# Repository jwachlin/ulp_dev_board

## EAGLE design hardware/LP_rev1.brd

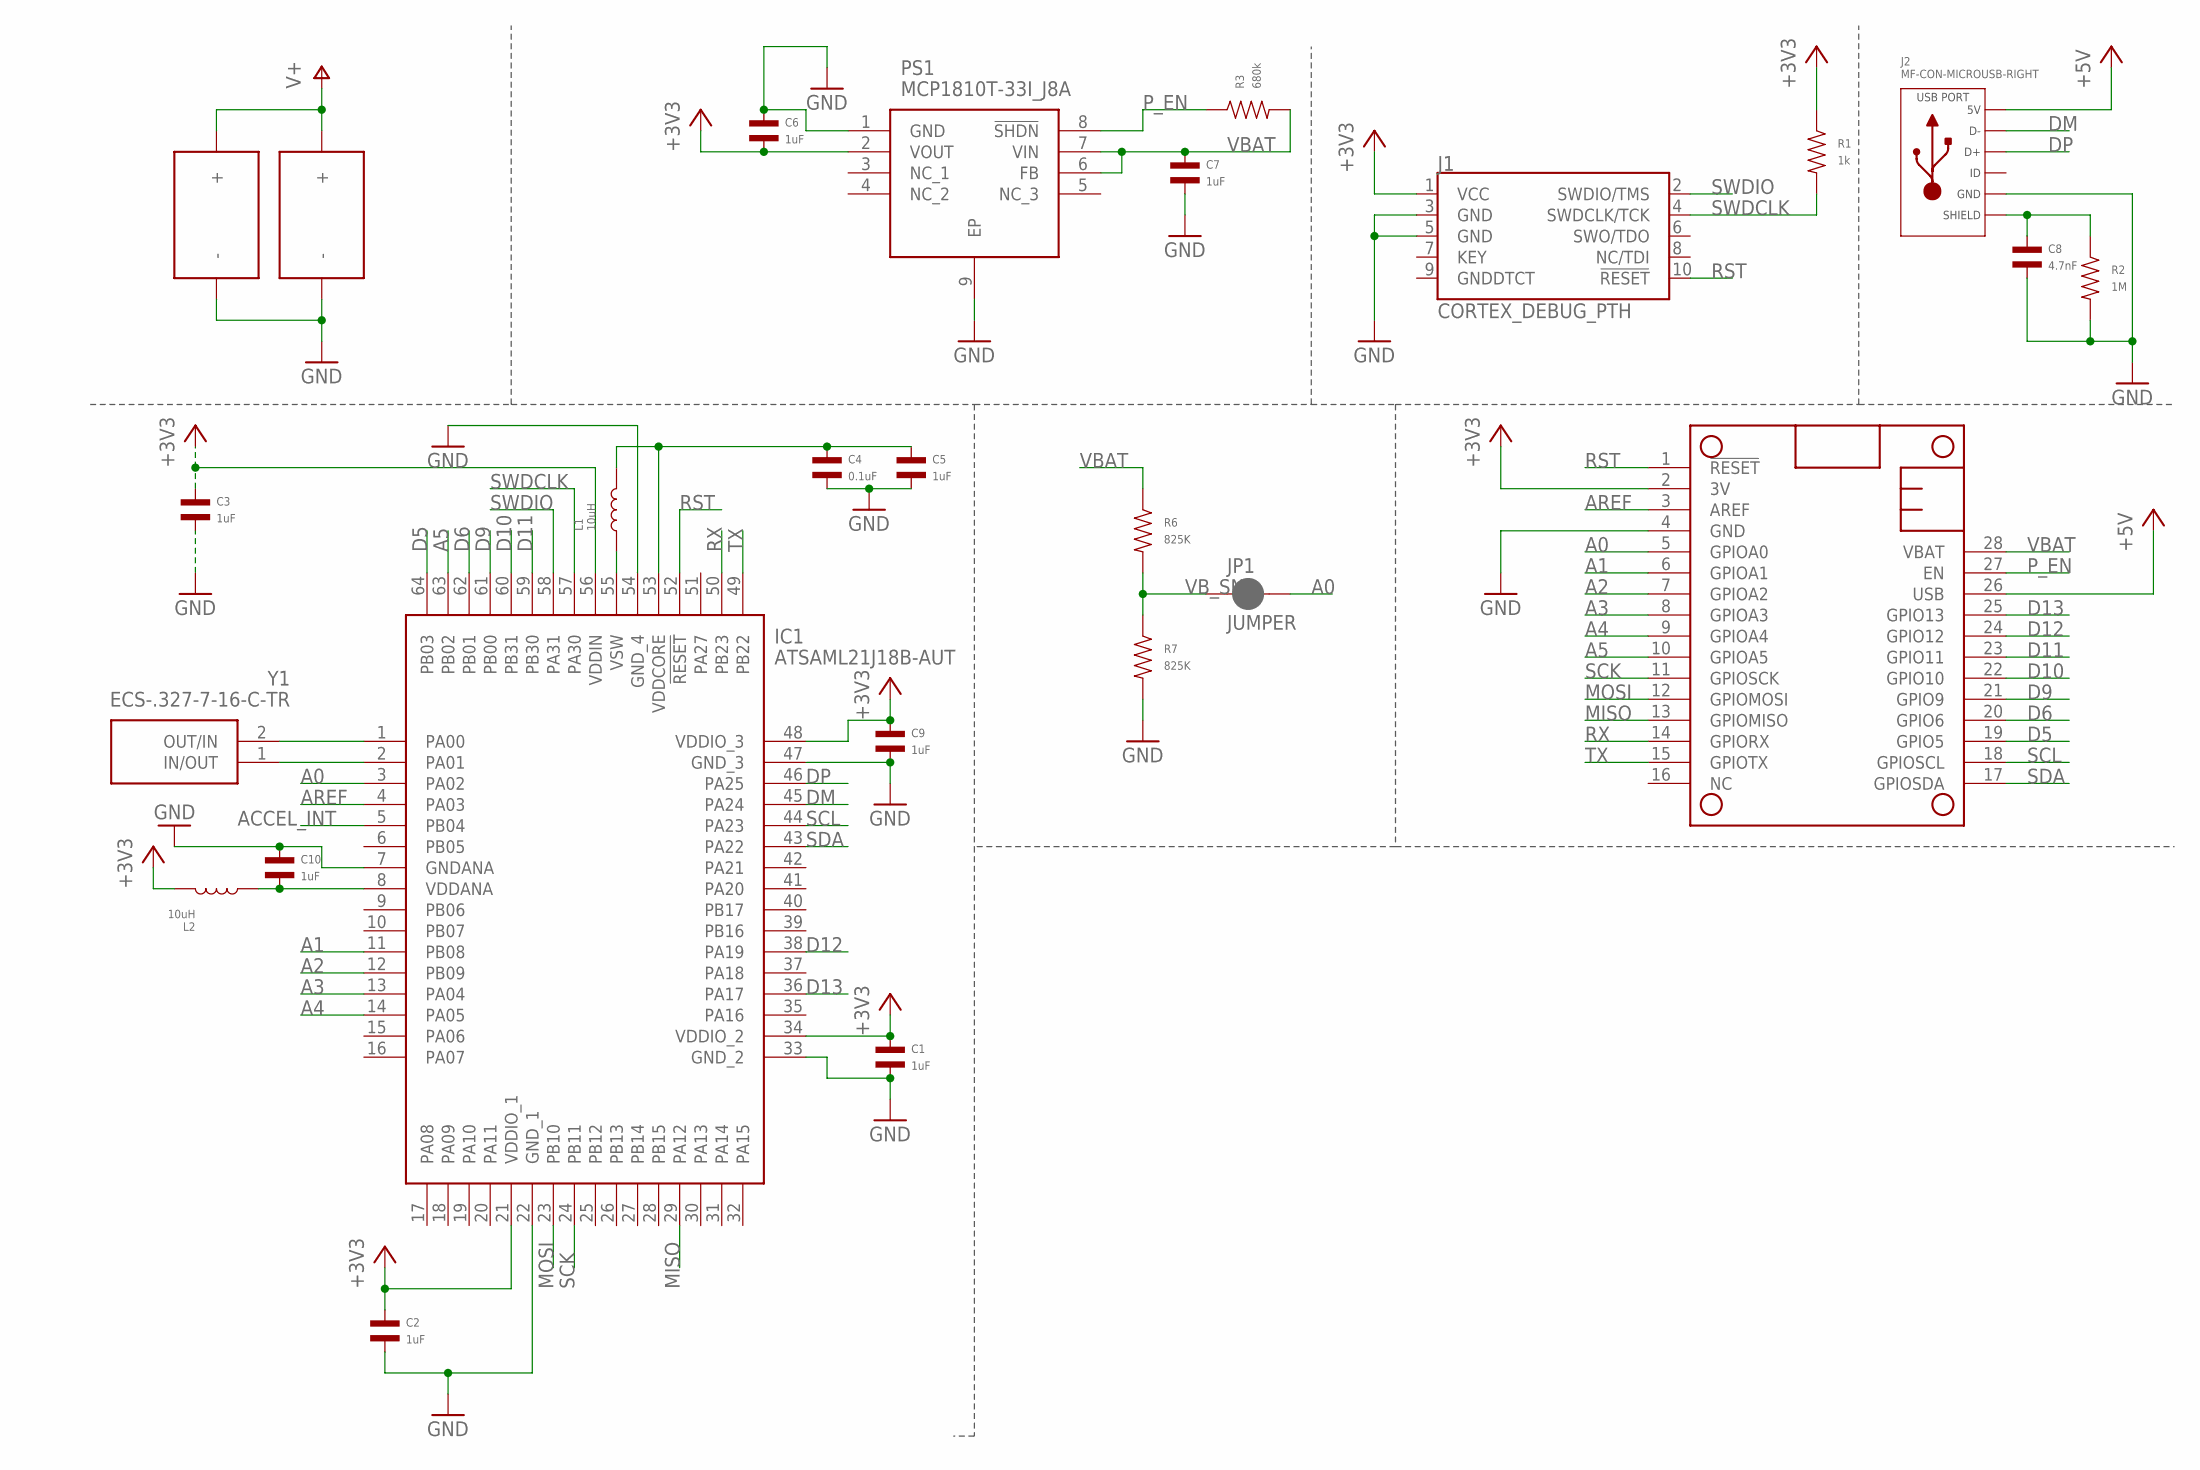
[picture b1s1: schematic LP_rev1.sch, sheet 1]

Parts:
C1, C2, C3, C5, C6, C7, C9, C10: 1uF; C0402
C4: 0.1uF; C0402
C8: 4.7nF; C0402
IC1: ATSAML21J18B-AUT; QFP50P1200X1200X120-64N
J1: CORTEX_DEBUG_PTH; 2X5-PTH-1.27MM
J2: MF-CON-MICROUSB-RIGHT; MICROUSB-RIGHT
JP1: JUMPER; SMT-JUMPER_2_NC_PASTE_NO-SILK
L1, L2: 10uH; L0603
MS1: FEATHERWING
PS1: MCP1810T-33I_J8A; SON50P200X200X90-9N
R1: 1k; R0402
R2: 1M; R0402
R3: 680k; R0402
R6, R7: 825K; R0402
U$1, U$2: KXOB25-01X8F
Y1: ECS-.327-7-16-C-TR; ECS327516TR

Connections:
+3V3: C1.P$1, C2.P$1, C3.P$1, C6.P$2, C9.P$1, IC1.21 (VDDIO_1), IC1.34 (VDDIO_2), IC1.48 (VDDIO_3), IC1.56 (VDDIN), J1.1 (VCC), L2.P$2, MS1.2 (3V), PS1.2 (VOUT), R1.P$1; also elsewhere on the board
+5V: J2.1 (5V), MS1.26 (USB)
A0: IC1.3 (PA02), JP1.2, MS1.5 (GPIOA0)
A1: IC1.11 (PB08), MS1.6 (GPIOA1)
A2: IC1.12 (PB09), MS1.7 (GPIOA2)
A3: IC1.13 (PA04), MS1.8 (GPIOA3)
A4: IC1.14 (PA05), MS1.9 (GPIOA4)
A5: IC1.63 (PB02), MS1.10 (GPIOA5)
ACCEL_INT: IC1.5 (PB04); also elsewhere on the board
AREF: IC1.4 (PA03), MS1.3 (AREF)
D5: IC1.64 (PB03), MS1.19 (GPIO5)
D6: IC1.62 (PB01), MS1.20 (GPIO6)
D9: IC1.61 (PB00), MS1.21 (GPIO9)
D10: IC1.60 (PB31), MS1.22 (GPIO10)
D11: IC1.59 (PB30), MS1.23 (GPIO11)
D12: IC1.38 (PA19), MS1.24 (GPIO12)
D13: IC1.36 (PA17), MS1.25 (GPIO13)
DM: IC1.45 (PA24), J2.2 (D-)
DP: IC1.46 (PA25), J2.3 (D+)
GND: C1.P$2, C2.P$2, C3.P$2, C4.P$2, C5.P$2, C6.P$1, C7.P$2, C8.P$2, C9.P$2, C10.P$1, IC1.7 (GNDANA), IC1.22 (GND_1), IC1.33 (GND_2), IC1.47 (GND_3), IC1.54 (GND_4), J1.3 (GND), J1.5 (GND), J2.5 (GND), MS1.4 (GND), PS1.1 (GND), PS1.9 (EP), R2.P$2, R7.P$2, U$1.P$2 (-), U$2.P$2 (-); also elsewhere on the board
MISO: IC1.29 (PA12), MS1.13 (GPIOMISO)
MOSI: IC1.23 (PB10), MS1.12 (GPIOMOSI)
unnamed: C4.P$1, C5.P$1, IC1.53 (VDDCORE), L1.P$2
unnamed: IC1.1 (PA00), Y1.2 (OUT/IN)
unnamed: IC1.2 (PA01), Y1.1 (IN/OUT)
unnamed: C10.P$2, IC1.8 (VDDANA), L2.P$1
unnamed: C8.P$1, J2.S1 (SLD), J2.S2 (SLD), J2.S3 (SLD), J2.S4 (SLD), J2.S5 (SLD), J2.S6 (SLD), R2.P$1
unnamed: IC1.55 (VSW), L1.P$1
P_EN: MS1.27 (EN), PS1.8 (!SHDN), R3.P$1
RST: IC1.52 (!RESET), J1.10 (!RESET), MS1.1 (!RESET)
RX: IC1.50 (PB23), MS1.14 (GPIORX)
SCK: IC1.24 (PB11), MS1.11 (GPIOSCK)
SCL: IC1.44 (PA23), MS1.18 (GPIOSCL); also elsewhere on the board
SDA: IC1.43 (PA22), MS1.17 (GPIOSDA); also elsewhere on the board
SWDCLK: IC1.57 (PA30), J1.4 (SWDCLK/TCK), R1.P$2
SWDIO: IC1.58 (PA31), J1.2 (SWDIO/TMS)
TX: IC1.49 (PB22), MS1.15 (GPIOTX)
V+: U$1.P$1 (+), U$2.P$1 (+); also elsewhere on the board
VBAT: C7.P$1, MS1.28 (VBAT), PS1.6 (FB), PS1.7 (VIN), R3.P$2, R6.P$1; also elsewhere on the board
VB_SNS: JP1.1, R6.P$2, R7.P$1

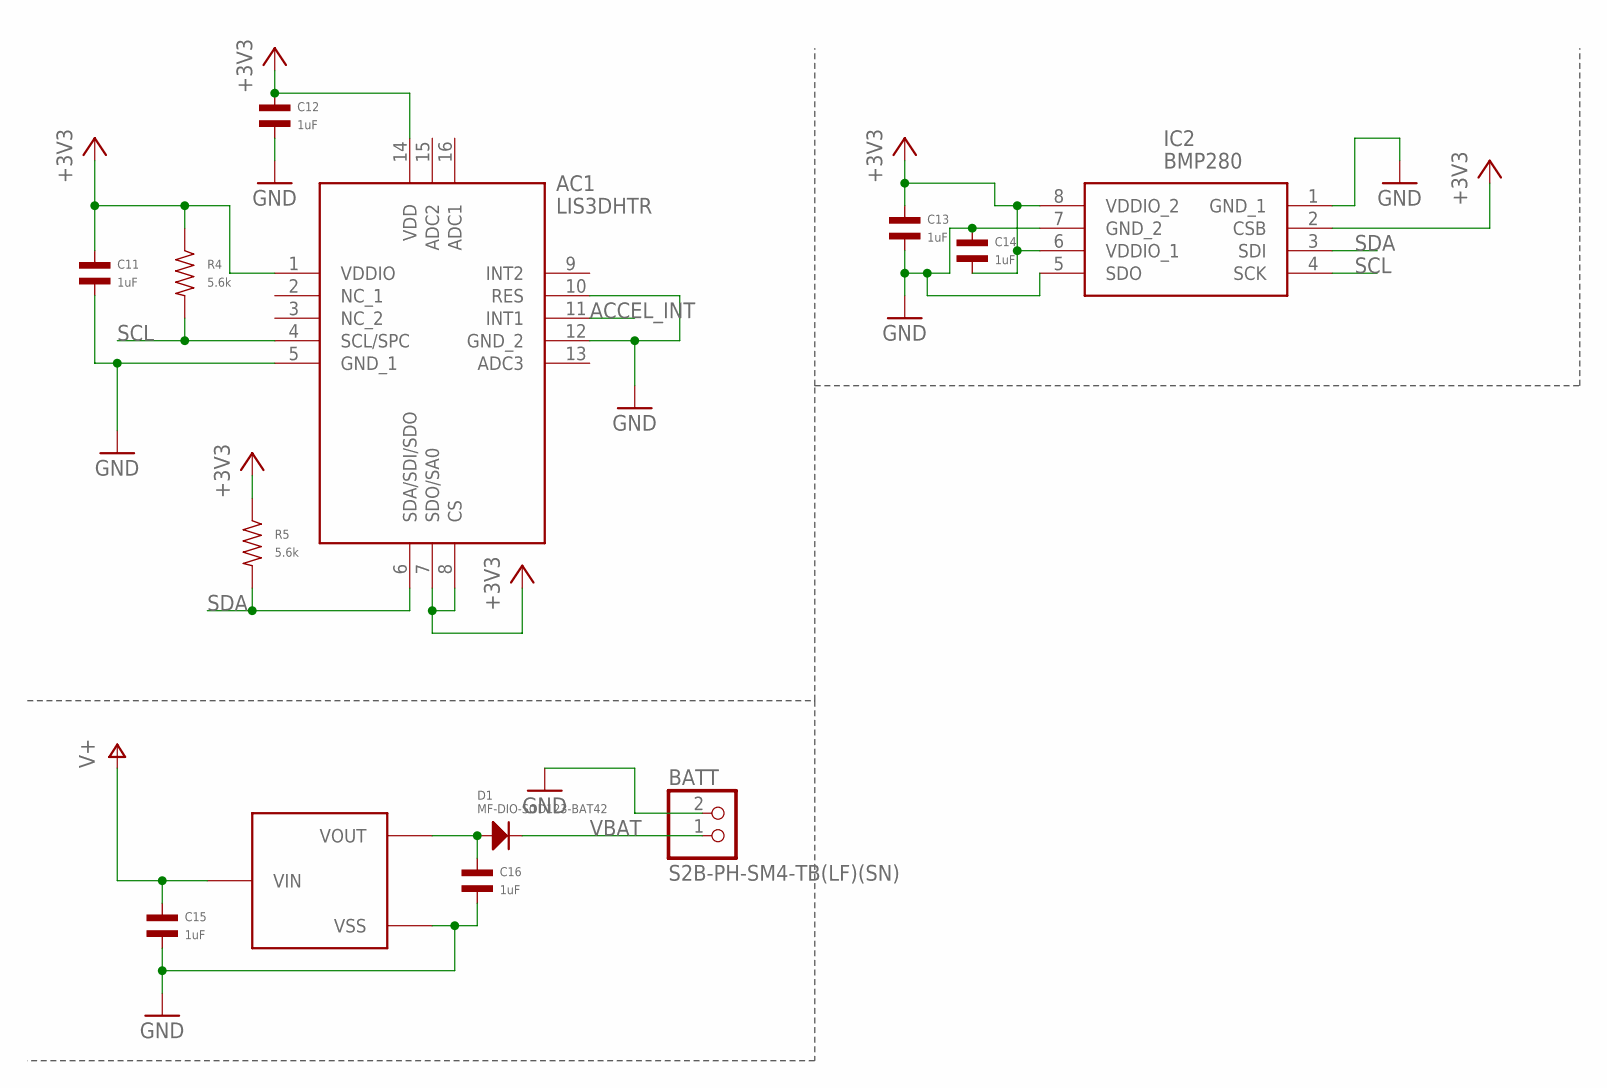
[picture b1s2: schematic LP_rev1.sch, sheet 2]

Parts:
AC1: LIS3DHTR; PQFN50P300X300X100-16N
BATT: S2B-PH-SM4-TB(LF)(SN); JST-PH-2-SMT-RA
C11, C12, C13, C14, C15, C16: 1uF; C0402
D1: MF-DIO-SOD123-BAT42; SOD-123
IC2: BMP280; 8-PIN-METAL-LID-LGA
R4, R5: 5.6k; R0402
U$3: XC6206P422MR-G; XC6206

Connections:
+3V3: AC1.1 (VDDIO), AC1.7 (SDO/SA0), AC1.8 (CS), AC1.14 (VDD), C11.P$1, C12.P$1, C13.P$1, C14.P$2, IC2.2 (CSB), IC2.6 (VDDIO_1), IC2.8 (VDDIO_2), R4.P$1, R5.P$1; also elsewhere on the board
ACCEL_INT: AC1.11 (INT1); also elsewhere on the board
GND: AC1.5 (GND_1), AC1.10 (RES), AC1.12 (GND_2), BATT.2 (1), C11.P$2, C12.P$2, C13.P$2, C14.P$1, C15.P$2, C16.P$2, IC2.1 (GND_1), IC2.5 (SDO), IC2.7 (GND_2), U$3.P$1 (VSS); also elsewhere on the board
unnamed: C16.P$1, D1.ANODE, U$3.P$2 (VOUT)
SCL: AC1.4 (SCL/SPC), IC2.4 (SCK), R4.P$2; also elsewhere on the board
SDA: AC1.6 (SDA/SDI/SDO), IC2.3 (SDI), R5.P$2; also elsewhere on the board
V+: C15.P$1, U$3.P$3 (VIN); also elsewhere on the board
VBAT: BATT.1 (2), D1.CATHODE; also elsewhere on the board

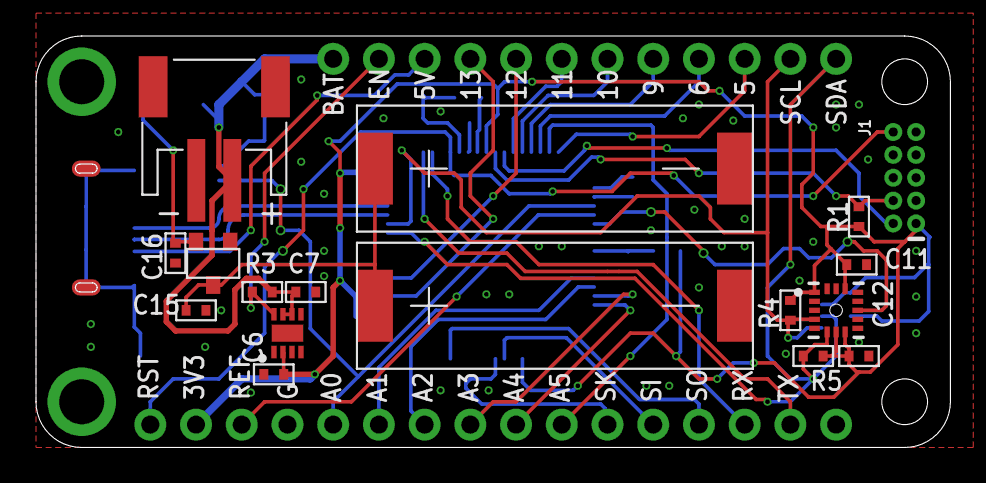
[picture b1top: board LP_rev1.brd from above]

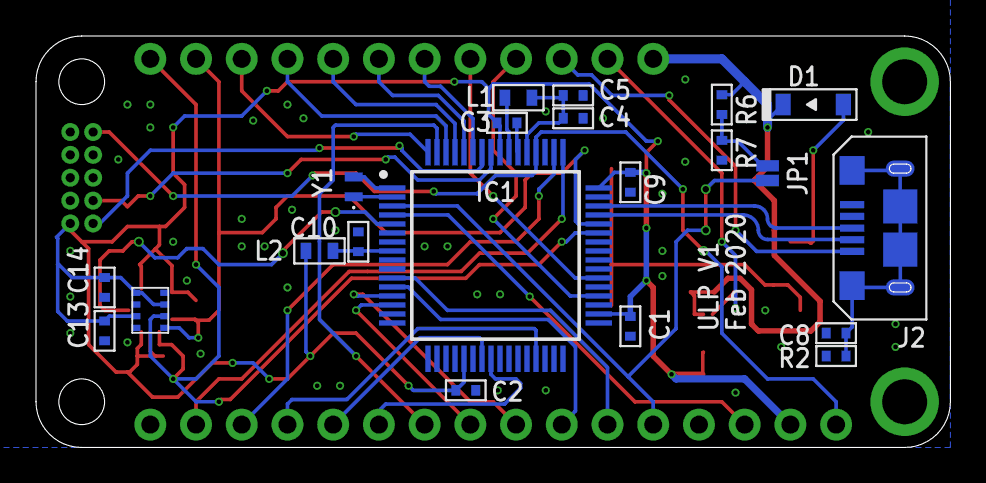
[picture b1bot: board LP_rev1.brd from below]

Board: 2 copper layers, 50.8 x 22.9 mm, 39 parts (21 on the bottom side), 41 nets.

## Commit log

2020-03-14 Adds revision 1 design

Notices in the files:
parts and their libraries:
SparkFun-Connectors: Licensing: Creative Commons ShareAlike 4.0 International - https://creativecommons.org/licenses/by-sa/4.0
